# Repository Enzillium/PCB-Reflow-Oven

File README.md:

# PCB-Reflow-Oven
A custom reflow oven using the 1400W HOMCOM mini 16L oven.

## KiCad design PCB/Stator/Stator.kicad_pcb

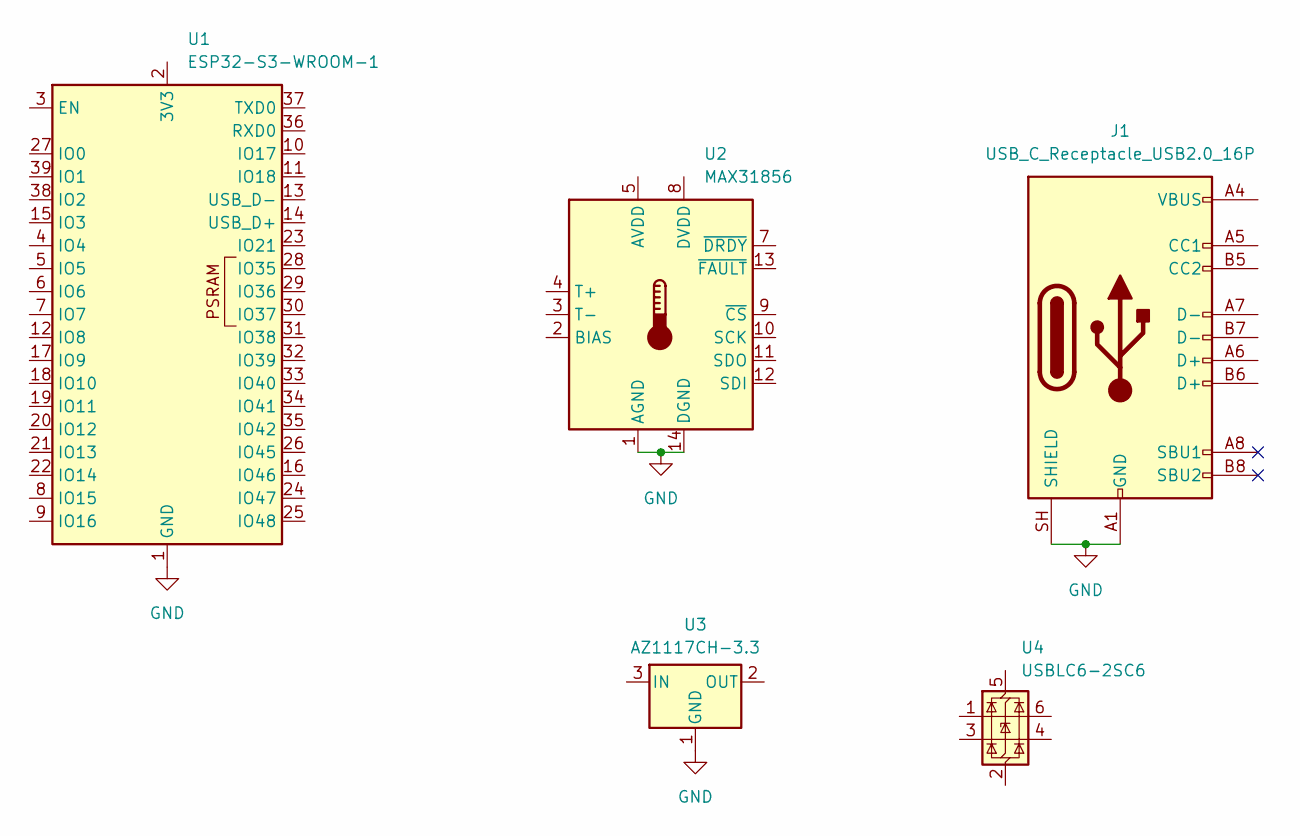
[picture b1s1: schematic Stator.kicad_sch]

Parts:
J1: USB_C_Receptacle_USB2.0_16P; USB_C_Receptacle_G-Switch_GT-USB-7010ASV
U1: ESP32-S3-WROOM-1; ESP32-S3-WROOM-1U
U2: MAX31856; TSSOP-14_4.4x5mm_P0.65mm
U3: AZ1117CH-3.3; SOT-223-3_TabPin2
U4: USBLC6-2SC6; SOT-23-6

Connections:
GND: J1.A1 (GND), J1.A12 (GND), J1.B1 (GND), J1.B12 (GND), J1.SH (SHIELD), U1.1 (GND), U1.40 (GND), U1.41 (GND), U2.1 (AGND), U2.14 (DGND), U3.1 (GND_1)
unnamed: J1.A4 (VBUS), J1.A9 (VBUS), J1.B4 (VBUS), J1.B9 (VBUS)

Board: 2 copper layers, 5 parts (0 on the bottom side), 2 nets, no tracks yet.
